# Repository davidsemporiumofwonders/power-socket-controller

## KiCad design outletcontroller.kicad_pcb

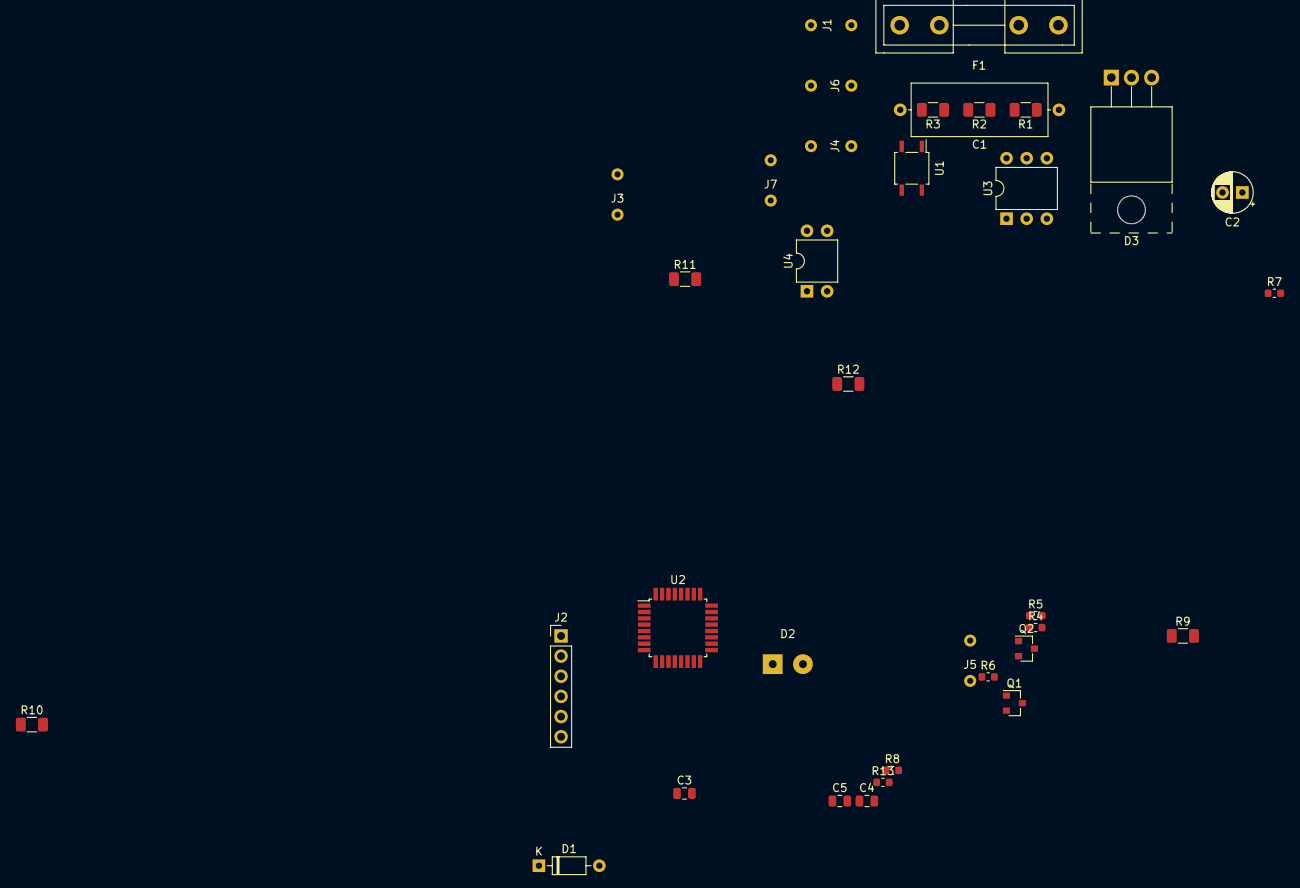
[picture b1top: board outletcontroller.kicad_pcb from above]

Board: 2 copper layers, 35 parts (0 on the bottom side), 27 nets, no tracks yet.

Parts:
C1: 0.47u; C_Axial_L17.0mm_D6.5mm_P20.00mm_Horizontal
C2: 220u; CP_Radial_D5.0mm_P2.50mm
C3, C4, C5: 100n; C_0805_2012Metric
D1: Zener_5v; D_DO-35_SOD27_P7.62mm_Horizontal
D2: 1n4148; SolderWirePad_1x02_P3.81mm_Drill1mm
D3: Q_SCR_AKG; TO-220-3_Horizontal_TabUp
F1: Fuse; Fuseholder5x20_horiz_open_inline_Type-I
J1, J3, J4, J5, J6, J7: Conn_01x01; spade_4.8mm
J2: Conn_01x06; PinHeader_1x06_P2.54mm_Vertical
Q1, Q2: MMBT3906; SOT-23
R1, R2, R3: 100k; R_1206_3216Metric
R4: 2k2; R_0603_1608Metric
R5: 110k; R_0603_1608Metric
R6: 100; R_0603_1608Metric
R7, R8: 330; R_0603_1608Metric
R9, R10, R11, R12: 15k; R_1206_3216Metric
R13: 20k; R_0603_1608Metric
U1: Bridge_12ac_3+_4-; SOP-4_3.8x4.1mm_P2.54mm
U2: ATmega88-20AU; TQFP-32_7x7mm_P0.8mm
U3: MOC3051M; DIP-6_W7.62mm
U4: EL814; DIP-4_W7.62mm

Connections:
Earth: J4.1, J7.1
GND: C2.2, C3.2, C4.2, C5.2, D1.2, D2.1, J2.6, R5.2, U1.4, U2.3, U2.5, U2.21, U3.2, U4.3
LINE: C1.1, D3.1, F1.1, R1.1, R7.1, R9.2
NEUT: J3.1, J6.1, R6.2, R11.2
unnamed: C1.2, R3.2, U1.2
unnamed: D2.2, Q1.3, U2.23
unnamed: D3.2, J5.1
unnamed: D3.3, U3.4
unnamed: F1.2, J1.1
unnamed: J2.2, U2.14
unnamed: J2.3, U2.15
unnamed: J2.4, U2.16
unnamed: J2.5, U2.17
unnamed: Q1.1, Q2.1, Q2.3, R5.1
unnamed: R1.2, R2.1
unnamed: R2.2, R3.1
unnamed: R4.2, U1.3
unnamed: R6.1, U1.1
unnamed: R7.2, U3.6
unnamed: R8.1, U2.13
unnamed: R8.2, U3.1
unnamed: R10.1, U4.1
unnamed: R9.1, R10.2
unnamed: R11.1, R12.2
unnamed: R12.1, U4.2
unnamed: R13.1, U2.32, U4.4
VCC: C2.1, C3.1, C4.1, C5.1, D1.1, J2.1, Q1.2, Q2.2, R4.1, R13.2, U2.4, U2.6, U2.18, U2.20
